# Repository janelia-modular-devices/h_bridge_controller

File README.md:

# h_bridge_controller

Authors:

    Peter Polidoro <polidorop@janelia.hhmi.org>

License:

    BSD

## More Detailed Help on Installation and Usage

[modular-devices](https://github.com/janelia-modular-devices/modular-devices)

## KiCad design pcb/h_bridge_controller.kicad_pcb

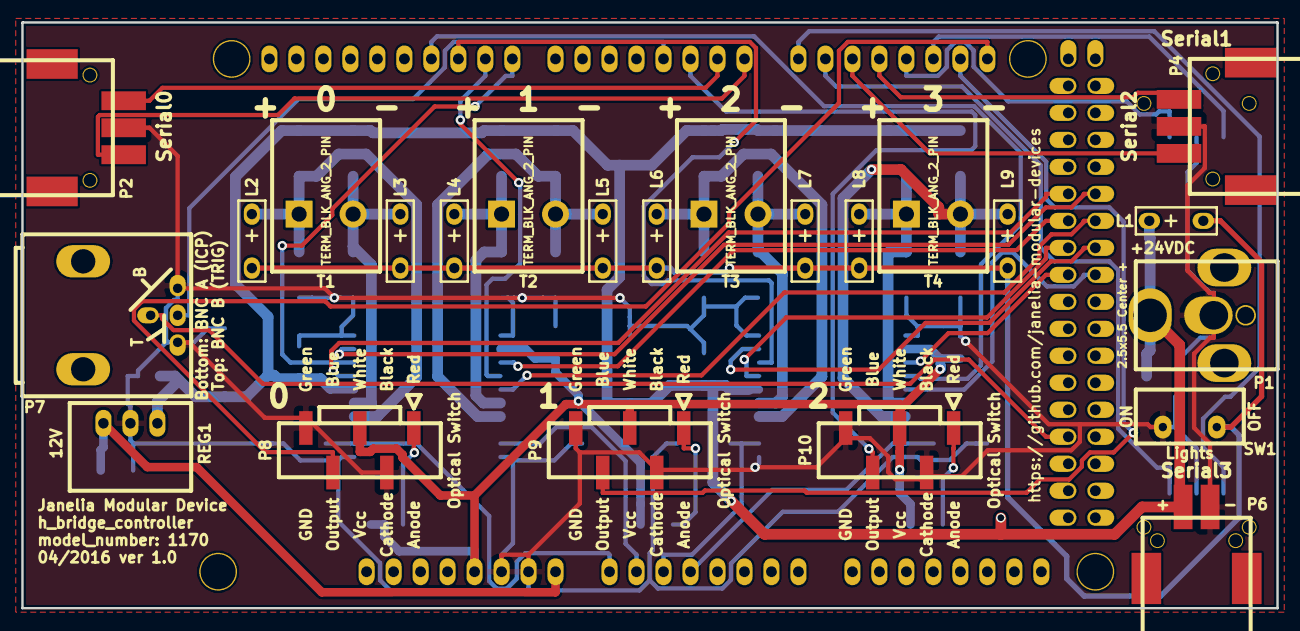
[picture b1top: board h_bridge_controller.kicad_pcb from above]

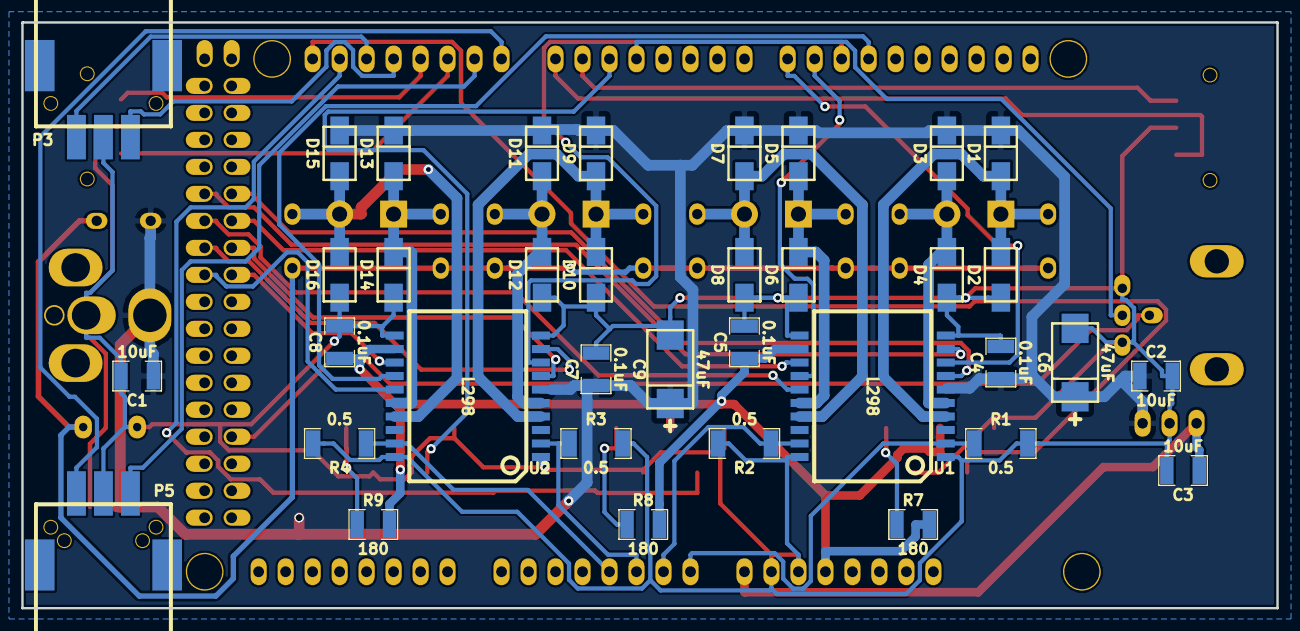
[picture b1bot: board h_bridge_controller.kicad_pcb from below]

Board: 2 copper layers, 118.1 x 55.1 mm, 60 parts (36 on the bottom side), 45 nets.

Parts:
ARDUINO1: ARDUINO_MEGA; ARDUINO_MEGA_SHIELD
C1, C2, C3: 10uF; SM1210
C4, C5, C7, C8: 0.1uF; SM1210
C6, C9: 47uF; SM2917_POL
D1, D2, D3, D4, D5, D6, D7, D8, D9, D10, D11, D12, D13, D14, D15, D16: diode_schottky_40V_1A; DO-214AC(SMA)
L1, L2, L3, L4, L5, L6, L7, L8, L9: LED_24V; LED_555-3XXX
P1: PWR_JACK_2.5x5.5; DCJACK_2PIN_HIGHCURRENT
P2, P3, P4, P5: HEADER_01X03_SMD_RA; Header_3_Pin_SMD_RA
P6: HEADER_01X02_SMD_RA; Header_2_Pin_SMD_RA
P7: BNC_DOUBLE_RA; BNC_DOUBLE
P8, P9, P10: HEADER_01X05_SMD_SHR; Header_Shrouded_5_Pin_SMD
R1, R2, R3, R4: 0.5; SM2010
R7, R8, R9: 180; SM1210
REG1: CONV_DC_DC_12V_1A; DC_DC_CONV_R78C
SW1: SPST_SLIDE_AS
T1, T2, T3, T4: TERM_BLK_ANG_2_PIN
U1, U2: L298; POWERSO20

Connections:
+5V: ARDUINO1.5V_1, C5.1, C8.1, P8.3, P9.3, P10.3, R7.2, R8.2, R9.2, U1.12, U2.12
/BNC_A: ARDUINO1.48, P7.1
/BNC_B: ARDUINO1.3, P7.3
/DIR_0A: ARDUINO1.30, U1.7
/DIR_0B: ARDUINO1.31, U1.9
/DIR_1A: ARDUINO1.32, U1.13
/DIR_1B: ARDUINO1.33, U1.15
/DIR_2A: ARDUINO1.34, U2.7
/DIR_2B: ARDUINO1.35, U2.9
/DIR_3A: ARDUINO1.36, U2.13
/DIR_3B: ARDUINO1.37, U2.15
/ENABLE_0: ARDUINO1.8, U1.8
/ENABLE_1: ARDUINO1.9, U1.14
/ENABLE_2: ARDUINO1.10, U2.8
/ENABLE_3: ARDUINO1.11, U2.14
/LED_GND: L1.2, L2.2, L3.2, L4.2, L5.2, L6.2, L7.2, L8.2, L9.2, SW1.3
/OUT_0+: D1.2, D2.1, L2.1, T1.1, U1.4
/OUT_0-: D3.2, D4.1, L3.1, T1.2, U1.5
/OUT_1+: D5.2, D6.1, L4.1, T2.1, U1.16
/OUT_1-: D7.2, D8.1, L5.1, T2.2, U1.17
/OUT_2+: D9.2, D10.1, L6.1, T3.1, U2.4
/OUT_2-: D11.2, D12.1, L7.1, T3.2, U2.5
/OUT_3+: D13.2, D14.1, L8.1, T4.1, U2.16
/OUT_3-: D15.2, D16.1, L9.1, T4.2, U2.17
/RX0: ARDUINO1.0, P2.1
/RX1: ARDUINO1.19, P3.1
/RX2: ARDUINO1.17, P4.1
/RX3: ARDUINO1.15, P5.1
/SENSE_0: ARDUINO1.A0, R1.1, U1.2
/SENSE_1: ARDUINO1.A1, R2.1, U1.19
/SENSE_2: ARDUINO1.A2, R3.1, U2.2
/SENSE_3: ARDUINO1.A3, R4.1, U2.19
/SW_0: ARDUINO1.21, P8.4
/SW_1: ARDUINO1.20, P9.4
/SW_2: ARDUINO1.2, P10.4
/TX0: ARDUINO1.1, P2.3
/TX1: ARDUINO1.18, P3.3
/TX2: ARDUINO1.16, P4.3
/TX3: ARDUINO1.14, P5.3
/V_IN: ARDUINO1.V_IN, C3.1, REG1.3
GND: ARDUINO1.GND1, ARDUINO1.GND2, C1.2, C2.2, C3.2, C4.2, C5.2, C6.2, C7.2, C8.2, C9.2, D2.2, D4.2, D6.2, D8.2, D10.2, D12.2, D14.2, D16.2, P1.2, P2.2, P3.2, P4.2, P5.2, P6.1, P7.2, P7.4, P8.2, P8.5, P9.2, P9.5, P10.2, P10.5, R1.2, R2.2, R3.2, R4.2, REG1.2, SW1.1, U1.1, U1.10, U1.11, U1.20, U2.1, U2.10, U2.11, U2.20
unnamed: P8.1, R7.1
unnamed: P9.1, R8.1
unnamed: P10.1, R9.1
VAA: C1.1, C2.1, C4.1, C6.1, C7.1, C9.1, D1.1, D3.1, D5.1, D7.1, D9.1, D11.1, D13.1, D15.1, L1.1, P1.1, P6.2, REG1.1, U1.6, U2.6

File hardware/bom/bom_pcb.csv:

Item,Reference(s),Value,Quantity,Description,PartNumber,Vendor
1,ARDUINO1,ARDUINO_MEGA,1,BOARD MCU MEGA2560,1050-1018-ND,digikey
2,C1 C2 C3,10uF,3,CAP CER 10UF 50V 10% X7S 1210,445-4536-1-ND,digikey
3,C4 C5 C7 C8,0.1uF,4,CAP CER 0.1UF 50V 10% X7R 1210,478-3586-1-ND,digikey
4,C6 C9,47uF,2,CAP TANT 47UF 35V 10% 2917,399-3821-1-ND,digikey
5,D1 D10 D11 D12 D13 D14 D15 D16 D2 D3 D4 D5 D6 D7 D8 D9,diode_schottky_40V_1A,16,DIODE SCHOTTKY 40V 1A SMA,SS14CT-ND,digikey
6,L1 L2 L3 L4 L5 L6 L7 L8 L9,LED_24V,9,LED 2MM 24V VERTICAL RED PC MNT,350-1723-ND,digikey
7,P1,PWR_JACK_2.5x5.5,1,CONN PWR JACK DC 2.5X5.5 8A T/H,CP-063BH-ND,digikey
8,P10 P8 P9,HEADER_01X05_SMD_SHR,3,CONN HEADER .100 VERT 5POS SMD,WM7205-ND,digikey
9,P2 P3 P4 P5,HEADER_01X03_SMD_RA,4,CONN HEADER 3POS R/A SMD GOLD,A100890CT-ND,digikey
10,P6,HEADER_01X02_SMD_RA,1,CONN HEADER 2POS R/A SMD GOLD,A100903CT-ND,digikey
11,P7,BNC_DOUBLE_RA,1,CONN BNC JACK R/A 75 OHM PCB,ACX1655-ND,digikey
12,R1 R2 R3 R4,0.5,4,RES SMD 0.5 OHM 1% 1W 2010,CSRN2010FKR500CT-ND,digikey
13,R7 R8 R9,180,3,RES SMD 180 OHM 5% 1/2W 1210,P180VCT-ND,digikey
14,REG1,CONV_DC_DC_12V_1A,1,CONV DC/DC 1A 12V OUT SIP VERT,945-1392-5-ND,digikey
15,SW1,SPST_SLIDE_AS,1,SWITCH SLIDE SPST 0.4VA 28V,360-2610-ND,digikey
16,T1 T2 T3 T4,TERM_BLK_ANG_2_PIN,4,TERMINAL BLOCK PCB 2POS 5.08MM,277-5716-ND,digikey
17,U1 U2,L298,2,IC BRIDGE DRIVER PAR 20POWERSO,497-3624-1-ND,digikey

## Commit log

2016-02-11 Initial commit.
2016-02-11 Removed code.
2016-02-11 Added pulse method.
2016-02-11 Added getDigitalInput method.
2016-02-25 Added interrupts.
2016-02-26 Added pwm method.
2016-03-07 Added toggling of both bridges.
2016-03-15 Added initial pcb files and moved firmware files.
2016-03-15 Progress towards pcb v1.0.
2016-04-06 Use relay_controller as pcb base.
2016-04-06 relay_controller -> h_bridge_controller.
2016-04-06 Progress towards pcb1.0.
2016-04-08 More progress towards pcb1.0.
2016-04-11 Finished pcb1.0.
2016-04-11 Updated bom.
2016-04-25 Added images.
2016-04-26 Modified for modular device hardware.
2016-04-27 Updated pulse constants.
2016-04-28 Progress towards pulse pattern.
2016-04-29 Added getPulseInfo method.
2016-04-29 Updated saved variable values before using.
2016-05-02 Add setPolarityReversed method.
2016-05-03 Removed testing code.
2016-05-20 Progress towards working with new ModularServer.
2016-05-31 Progress towards updated firmware.
2016-05-31 Basic functionality.
2016-05-31 Added pulse and addPwmPeriodOnDuration methods.
2016-05-31 Set field units.
2016-09-19 Updated spacing around pointers and references.
2016-09-19 Updated field documentation.
2016-09-21 pcb -> hardware.
2016-09-22 Moved to mega hardware directory.
2016-09-22 Updated to work with ModularServer changes.
2016-09-22 Progress in rung_wheel.
2016-10-03 Added firmware/HBridgeController.
2016-10-05 Updated firmware/HBridgeController.
2016-10-05 Added firmware/RungWheelController.
2016-10-19 Updated firmware/RungWheelController.
2016-10-19 Removed firmware/h_bridge_controller and firmware/rung_wheel.
2016-12-14 Updated firmware.
2017-03-06 Updated firmware/HBridgeController and firmware/RungWheelController.
2017-03-08 Added hardware/h_bridge_controller_3x2.
2017-03-29 Updated documentation.
2017-05-01 Updated firmware/*.
2017-11-20 janelia-idf -> janelia-experimental-technology
2018-04-12 Updated submodules.
2018-04-12 *.md -> *.org.
2018-05-18 Submodule update.
2018-08-12 polidorop@janelia.hhmi.org -> peterpolidoro@gmail.com
2018-08-27 Combined software and hardware licenses.
2021-09-17 Update email address
